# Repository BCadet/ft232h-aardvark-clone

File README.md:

# ft232h-aardvark-clone

A simple project to clone the TotalPhase Aardvark probe.
This repo contains the Kicad project files for a shield of the cjmcu-ft232h board.  

This shield provides two IDC10 connectors:
- one Aardvark-like connector for SPI/I2C communication
- one AZ-Delivery logic Analizer connector

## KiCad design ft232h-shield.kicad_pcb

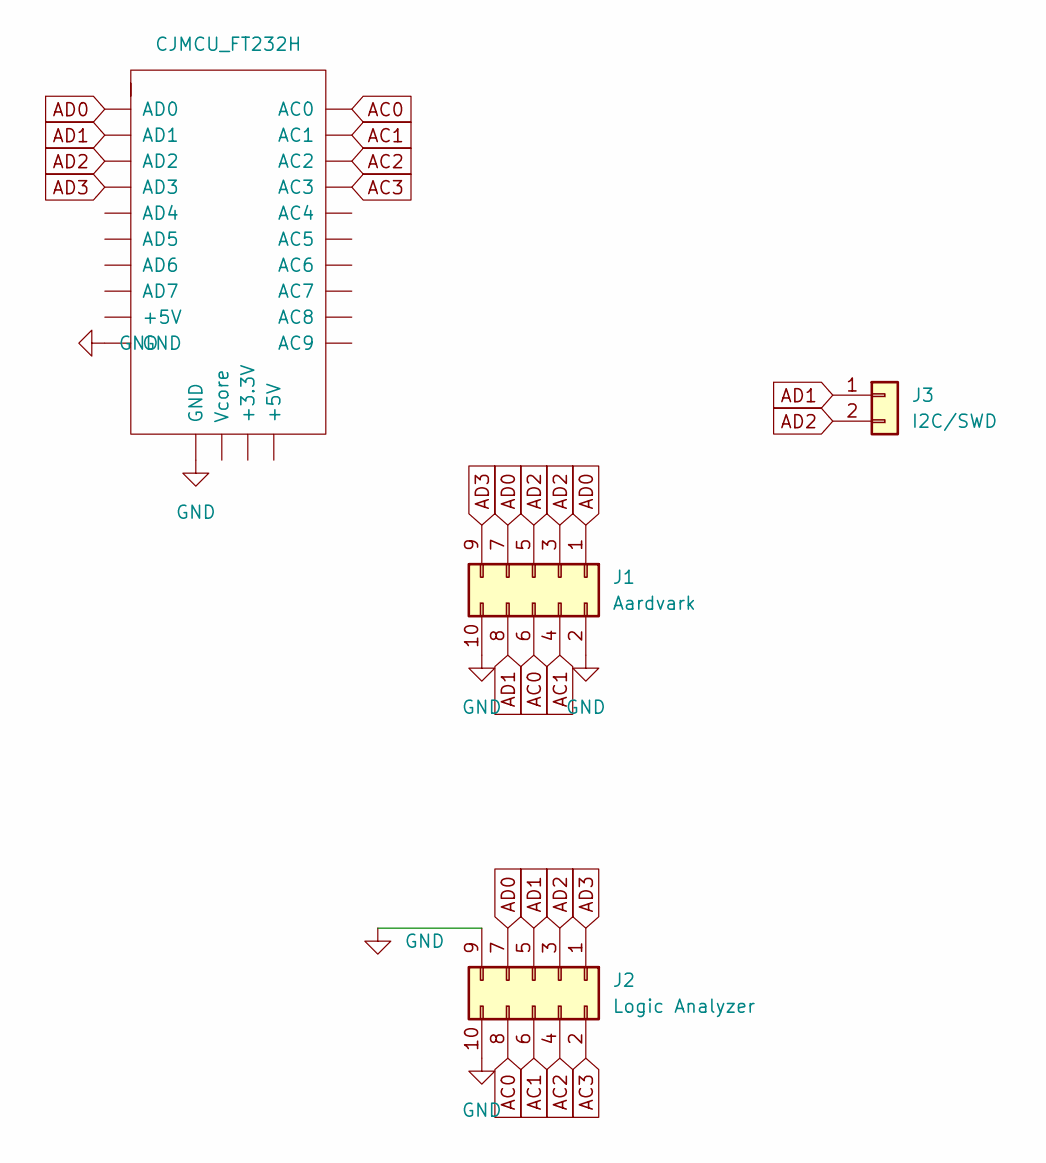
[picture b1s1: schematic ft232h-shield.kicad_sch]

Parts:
CJMCU_FT1: CJMCU_FT232H
J1: Aardvark; IDC-Header_2x05_P2.54mm_Vertical
J2: Logic Analyzer; IDC-Header_2x05_P2.54mm_Vertical
J3: I2C/SWD; PinHeader_1x02_P2.54mm_Vertical

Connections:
AC0: CJMCU_FT1.AC0, J1.6, J2.8
AC1: CJMCU_FT1.AC1, J1.4, J2.6
AC2: CJMCU_FT1.AC2, J2.4
AC3: CJMCU_FT1.AC3, J2.2
AD0: CJMCU_FT1.AD0, J1.1, J1.7, J2.7
AD1: CJMCU_FT1.AD1, J1.8, J2.5, J3.1
AD2: CJMCU_FT1.AD2, J1.3, J1.5, J2.3, J3.2
AD3: CJMCU_FT1.AD3, J1.9, J2.1
GND: CJMCU_FT1.GND1 (GND), CJMCU_FT1.GND2 (GND), J1.2, J1.10, J2.9, J2.10

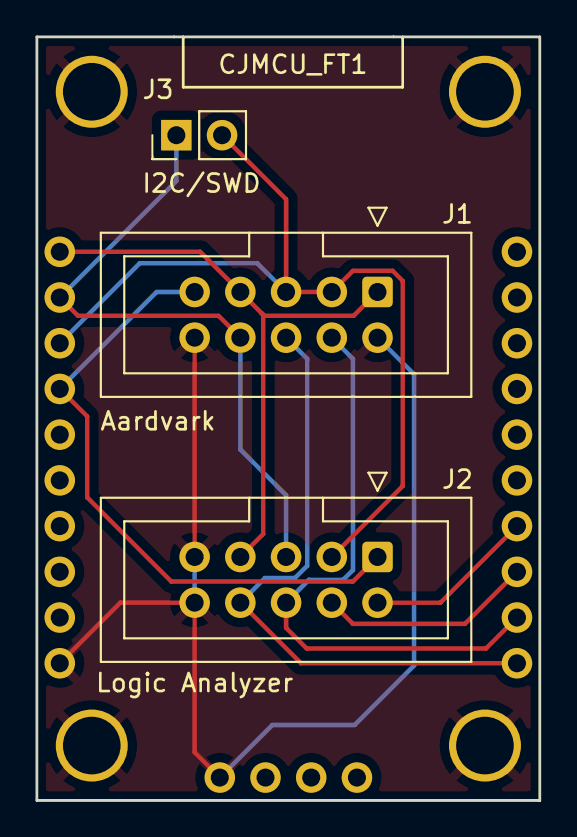
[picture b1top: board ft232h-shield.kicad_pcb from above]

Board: 2 copper layers, 27.9 x 42.4 mm, 4 parts (0 on the bottom side), 9 nets.

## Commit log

2023-01-12 initial
2023-01-12 add README
2023-01-12 Create LICENSE
